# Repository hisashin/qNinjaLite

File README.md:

# Open Source $50 qLAMP machine qNinja

# $300 Real Time PCR and LAMP machine "[qNinja](https://github.com/hisashin/qNinja)" is also available

## Reference Links
- [qNinja portal](https://qninja.hisa.dev)

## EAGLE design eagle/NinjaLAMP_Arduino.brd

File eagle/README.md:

*Schematic*

*Layout for PCB*

*Layout for hand wiring*

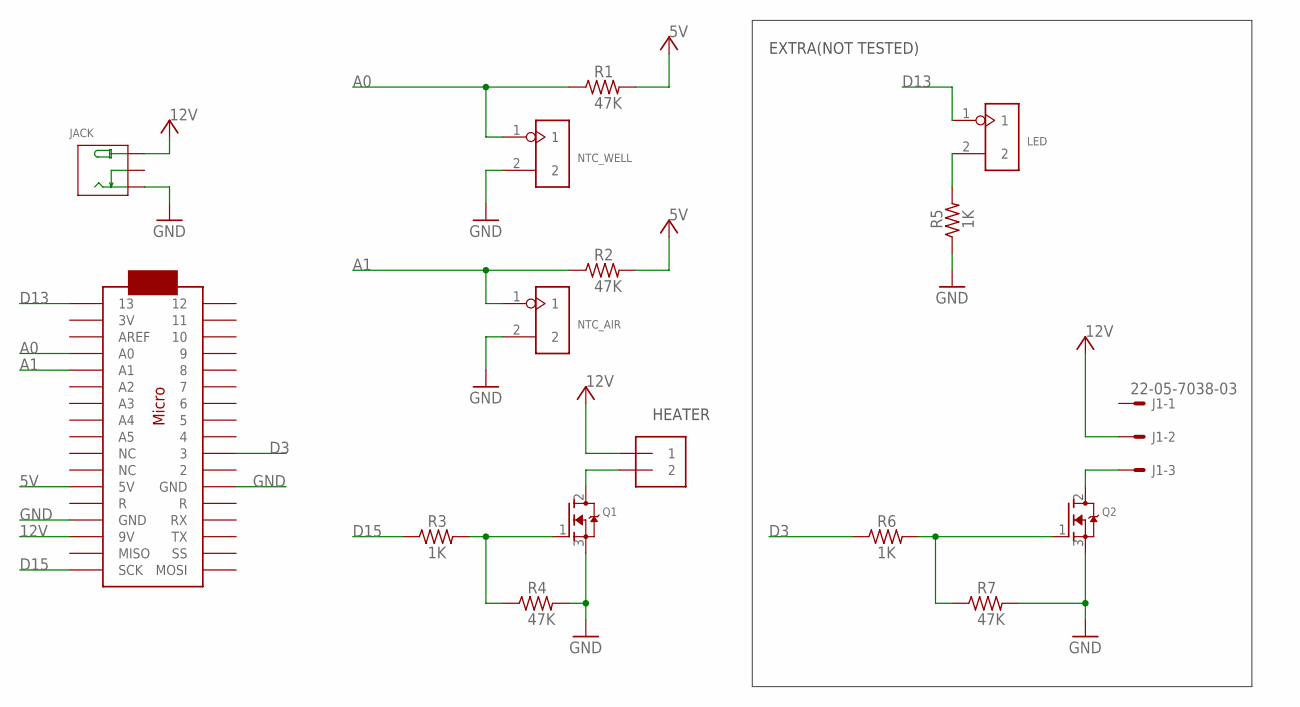
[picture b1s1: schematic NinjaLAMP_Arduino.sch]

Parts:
HEATER: 1X2-3.5MM
J1: 22-05-7038-03; 7395-03
JACK: DC-005; DCJ3P-14.2X11.0X9.0MM
LED: 2p-2.54; H2-2.54
NTC_AIR: 2p-2.54; H2-2.54
NTC_WELL: 2p-2.54; H2-2.54
Q1, Q2: MOSFET-NGDS_TO220V; TO220V
R1, R2, R4, R7: 47K; 0204/7
R3, R5, R6: 1K; 0204/7
U$2: ARDUINOMICRO

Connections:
5V: R1.2, R2.2, U$2.P$23 (5V)
12V: HEATER.1, J1.2, JACK.+B (+), JACK.+T (+), U$2.P$20 (9V)
A0: NTC_WELL.1, R1.1, U$2.P$31 (A0)
A1: NTC_AIR.1, R2.1, U$2.P$30 (A1)
D3: R6.1, U$2.P$10 (3)
D13: LED.1, U$2.P$34 (13)
D15: R3.1, U$2.P$18 (SCK)
DRAIN: HEATER.2, Q1.2 (D)
GATE: Q1.1 (G), R3.2, R4.1
GND: JACK.-1B (-), JACK.-1T (-), NTC_AIR.2, NTC_WELL.2, Q1.3 (S), Q2.3 (S), R4.2, R5.1, R7.2, U$2.P$12 (GND), U$2.P$21 (GND)
unnamed: LED.2, R5.2
unnamed: Q2.1 (G), R6.2, R7.1
unnamed: J1.3, Q2.2 (D)

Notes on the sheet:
EXTRA(NOT TESTED)
HEATER

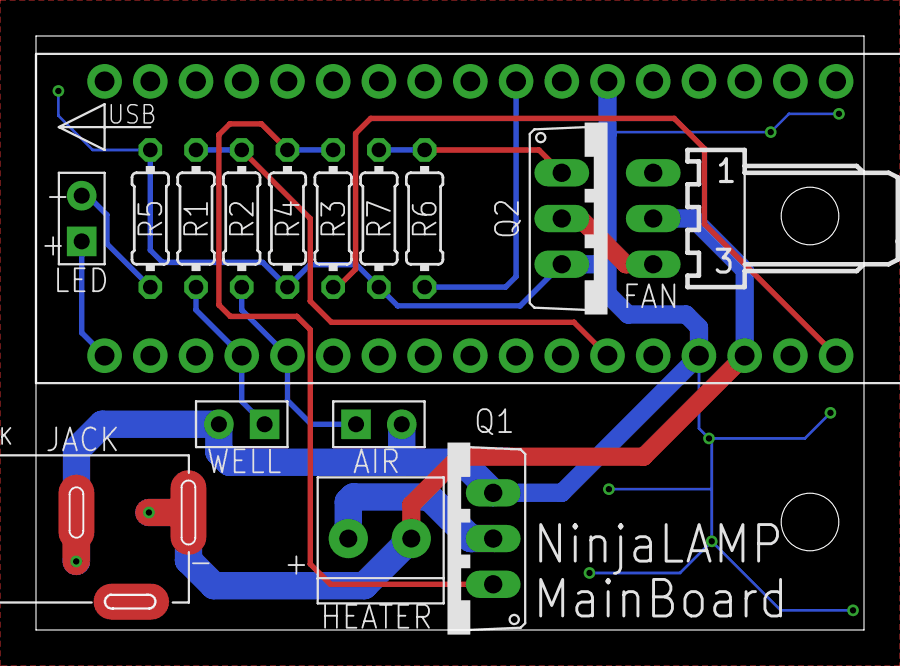
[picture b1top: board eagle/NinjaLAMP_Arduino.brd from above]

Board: 2 copper layers, 46.0 x 33.0 mm, 16 parts (0 on the bottom side), 13 nets.

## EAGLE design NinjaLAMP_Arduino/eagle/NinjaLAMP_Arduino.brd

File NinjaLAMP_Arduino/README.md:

# NinjaLAMP for Arduino

Make your own LAMP machine with Arduino.

- Why NinjaLAMP?
  - Precise temperature control with thermal simulation model sensing not only tube holder but air
  - Support different kinds of core parts guiding how to choose and calibrate to minimize error. Look "Advanced" below.
  - Easy to build. Only 4 resistors, 1 mosfet, 2 thermistors on [circuit](https://github.com/hisashin/NinjaLAMP/tree/master/NinjaLAMP_Arduino/eagle).
- [BOM (Bill of materials)](https://github.com/hisashin/NinjaLAMP/wiki/%5BArduino%5D-BOM) to buy
- 3d print [base](https://github.com/hisashin/NinjaLAMP/blob/master/NinjaLAMP_Arduino/3d/4x4_3d_base.stl) and [cover](https://github.com/hisashin/NinjaLAMP/blob/master/NinjaLAMP_Arduino/3d/4x4_3d_cover.stl) upside down without support ([3d model](https://gallery.autodesk.com/projects/149287/ninjalamp))
- Set target temperature
- [Upload source to Arduino](https://github.com/hisashin/NinjaLAMP/wiki/%5BArduino%5D-How-to-upload-the-software)
- Run and monitor temperature graph

### Advanced

- How to choose and calibrate different tube holder, heater, thermistor
- [How to use simulated sample temperature](https://github.com/hisashin/NinjaLAMP/wiki/How-to-use-simulated-sample-temperature)
- [How to customize source before uploading](https://github.com/hisashin/NinjaLAMP/wiki/%5BArduino%5D-How-to-customize-source-before-uploading)

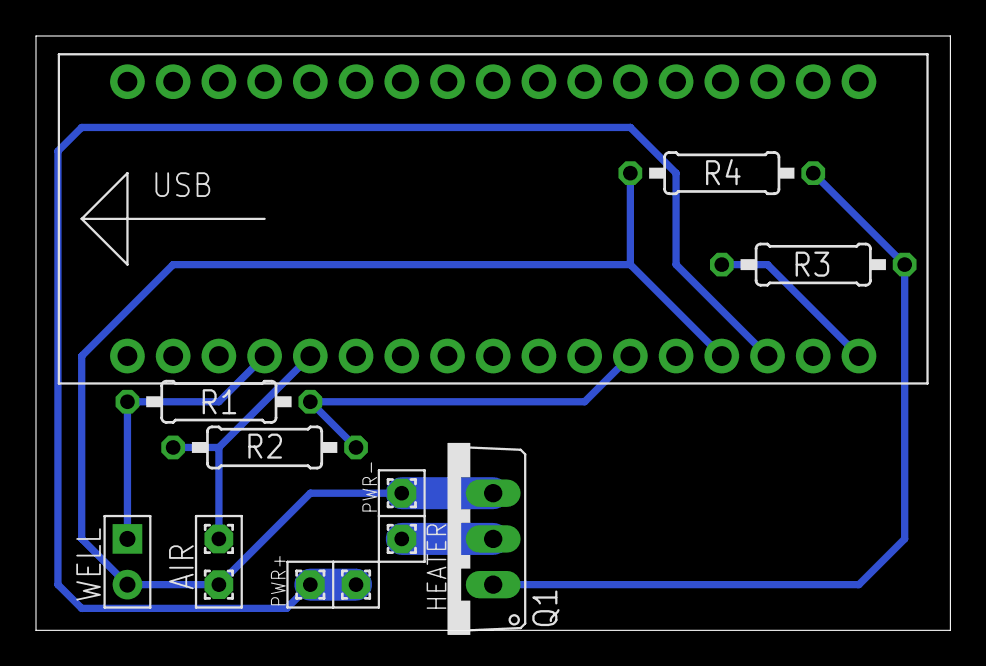
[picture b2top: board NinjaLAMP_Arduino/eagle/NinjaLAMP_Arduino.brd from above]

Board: 2 copper layers, 50.8 x 33.0 mm, 13 parts (0 on the bottom side), 8 nets.

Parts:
HEATER1, HEATER2: 1,6/0,8
NTC_AIR1, NTC_AIR2: 1,6/0,8
NTC_WELL: 2p-2.54; H2-2.54
POWER+: 1,6/0,8
POWER-: 1,6/0,8
Q1: TO220V
R1, R2, R4: 47K; 0207/10
R3: 1K; 0207/10
U$1: ARDUINOMICRO

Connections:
5V: R1.2, R2.2, U$1.P$23
12V: HEATER1.1, POWER+.1, U$1.P$20
A0: NTC_WELL.1, R1.1, U$1.P$31
A1: NTC_AIR1.1, R2.1, U$1.P$30
D15: R3.1, U$1.P$18
DRAIN: HEATER2.1, Q1.2
GATE: Q1.1, R3.2, R4.1
GND: NTC_AIR2.1, NTC_WELL.2, POWER-.1, Q1.3, R4.2, U$1.P$12

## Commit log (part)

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2020-04-27 update 3d model of Lite
2020-04-27 Implement start/stop commands
2020-04-27 Receive target temperature at "/start"
2020-04-27 Add index.html
2020-04-27 add stl data for Lite
2020-04-28 Separate ADC related functions as ADC and subclasses
2020-04-28 add eagle files
2020-04-28 add photos
2020-04-28 add 3d models
2020-04-28 Separage NinjaLAMPCore class
2020-04-28 Fix lib links / Call lib in NinjaLAMP_Arduino
2020-04-28 Fix thermistor conf (thermistors are placed to the "low" side)
2020-04-28 Move definition of PWM pin to the top
2020-04-28 Add README
2020-04-28 Add customization guide
2020-04-28 Add comments to main source file / Fix README
2020-04-28 add 3d stl
2020-04-28 add images
2020-04-29 Use symlinks to include ADC.h and NinjaLAMPCore.h/cpp
2020-04-29 Fill temp buffer before starting experiment
2020-04-29 Test
2020-04-29 Fixed a dead link
2020-04-29 Add a link to upload guide on Wiki
2020-04-29 Add image of "upload" button on Arduino IDE
2020-04-29 Add screenshot of Arduino serial monitor
2020-04-29 update 3d model : add cover
2020-04-30 add cover
2020-04-30 Add images (for customization guide)
2020-04-30 Replace images
2020-04-30 Add comments about bConstantRanges
2020-04-30 Add example connection image
2020-04-30 add belt
2020-04-30 replace photo to latest
2020-05-01 Implement temp simulation
2020-05-01 Fix merge failure
2020-05-01 Added an image for Wiki
2020-05-01 Added images for Wiki
2020-05-01 Add capture images for Wiki
2020-05-01 Move images to the right directory
2020-05-01 Add image
2020-05-01 Add illustration of heat simulation feature
2020-05-01 Add small images
2020-05-01 Add link to Wiki page
2020-05-01 New feature: Change target by serial message
2020-05-01 Add main graph (with serial target control)
2020-05-01 Add images (to illustrate how to use Arduino IDE's serial UI)
2020-05-01 Add a link to README page
2020-05-02 Arduino version become de fact NinjaLAMP
2020-05-02 Add images of Arduino's library manager
2020-05-02 Add public getters / Add elapsed time
2020-05-02 Support multiple stages
2020-05-03 Rename files (spec memo)
2020-05-03 Simplify spec memo
2020-05-03 Add URL of customization guide
2020-05-03 Add an image of thermal profile
2020-05-03 Add a link to "Experiments with multiple stages" article
2020-05-03 Add comments to getter functions
2020-05-03 Add a link to REAEMD.md (to Wiki article about output customization)
2020-05-04 t5.5 lasercut design finished
2020-05-04 eagle design finished
2020-05-04 add header
2020-05-04 remove old READMEs
2020-05-05 add simple lasercut model with t6.0mm
2020-05-16 add simple pcb
2020-05-20 add 3d model of tube_holder
2020-10-27 sync
2020-10-27 add ver1.0
2020-10-28 pcb ver1.0 complete
2020-10-29 added tacts and EEPROM
2020-10-30 added 1x8 and 2x8 iges
2020-11-06 add 3dprint data
2020-11-10 bigger footprint for polcap
2020-11-10 add todo memo
2020-11-11 Fix compilation error
2020-11-11 correct MOSFET pins
2020-11-13 add pdf and images of ver1.0 kicad
2020-11-13 Add hardware conf
2020-11-13 Define NXFT15WF104FA2B100 thermistor
2020-11-13 Implement hardware constructor (For first and second models)
2020-11-13 Define NTCG164KF104FT1S thermistor
2020-11-13 Define pins for XIAO model / Add document for LCD model
2020-11-13 add xiao example
2020-11-13 rename to README
2020-11-13 copy latest source to ver0.9 and ver1.0. They are identical at this point
2020-11-13 add image to explain version difference
2020-11-13 add image of ssd1306 library
2020-11-13 add image of xiao_example_gpio
2020-11-13 add image of xiao_example_eeprom
2020-11-13 make directory for ver0.9 and ver1.0
2020-11-13 make example directory
2020-11-13 rename to examples
2020-11-23 added example xiao_example_menu
2020-11-25 increased font size in xiao_example_menu
2020-11-25 restored sample items
2020-11-25 fixed manu name
2020-12-02 add photos and realistic menu
2020-12-12 Added lcdgfx library components to examples
2021-01-07 added utility to reset last eeprom byte, added gui_demo with initial implementation of top menu and default system configuration in eeprom
2021-01-14 initial implementation of menu
2021-01-24 Implemented edit cycle, add cycle, flip orientation and cycle run page
2021-01-25 Add a function resetting EEPROM / Clear GUI when going back to the top menu
2021-01-25 Comment-out RESET_EEPROM flag
2021-01-25 Remove unused dependency from NinjaLAMPCore lib
2021-01-26 Integrate gui_demo with NinjaLAMP core
2021-01-26 Implemented experiment management with LCD+buttons interface
2021-01-26 Add compressed core library and add how-to guide to the readme file
2021-01-26 Display temp, time and phase on the LCD
2021-01-26 Switch "Ramp", "Amplify" and "Stop" labels
2021-01-26 Call core->stop by choosing "Cancel" button on running screen
2022-03-03 just before import netlist to qLAMP-main-2x8
2022-03-03 renmaed
2022-03-03 renamed
2022-03-05 wiring
2022-03-07 dru cleared
2022-03-07 just before placing vias
2022-03-07 batch01 ready
2022-03-09 changing pd and demodulator
2022-03-10 prepare batch02/main with todo comments
2022-04-15 add equip pdf
2022-04-15 add links
2022-06-09 ordered batch2/main
2022-06-12 put latest well
2022-06-13 move dirs as qNinja
2022-06-13 move dirs unused anymore
2022-06-14 Add uPython code
2022-06-16 initialize batch03/main
2022-06-20 Add scheduler
2022-06-20 Add websocket to cycler
2022-06-26 add batch03 and batch02/pdf
2022-06-27 clear layout
2022-07-08 Add mqtt
2022-07-11 Support longer messages by MQTT
2022-08-12 just before ripup batch03/main
2022-08-12 wiring batch03/main
2022-08-14 wiring batch03/main done
2022-08-14 batch03 finished
2022-08-15 add pads below all pds
2022-08-17 add reg alt
2022-10-06 Add python files
2022-10-06 Add optics demo
2022-10-06 wiring batch04/main
2022-10-06 Add hardware control for batch3 design
2022-10-11 Implemented thermistor switching
2022-10-12 Workaround for PWM problems
2022-10-13 ordered batch04
2022-10-18 init batch05
2022-10-18 PID tuning
2022-10-26 Update PID logic
2022-10-26 Enable & disable buttons according to the device state
2022-10-27 update dxf
2022-11-01 PID control / UI
2022-11-01 Add cycler_mqtt
2022-11-03 Add LCD
2022-11-03 autodeploy
2022-11-03 Remove unused file
2022-11-04 Support batch4 pins
2022-11-04 Add console
2022-11-06 Move app files into app dir
2022-11-07 wired batch05/main
2022-11-08 thick holder to remove washers
2022-11-22 Support batch5 hardware
2022-11-22 Update web client
2022-11-22 Fix merge error
2022-11-23 Change app name
2022-11-23 Collapse advanced settings
2022-11-23 Update status bar layout
2022-11-23 Update form
2022-11-24 Add experiment protocol to event payload
2022-11-24 Add toasts
2022-11-24 Add advanced menu
2022-11-24 Change topic level (qninjalite->ninja)
2022-11-24 Add toasts to show connection status
2022-11-24 Shorten MQTT property names
2022-11-24 Shorten MQTT properties / Change file naming rule
2022-11-25 Shorten property names (final_hold_temp->h)
2022-11-25 Shorten property names (data_collection_interval->i)
2022-11-25 Shorten MQTT property names (data_collection -> c)
2022-11-25 Shorten property names (duration->d)
2022-11-25 Replace property names (temp->t)
2022-11-25 Replace property name (steps->s)
2022-11-25 Update default protocol
2022-11-25 Replace property names (PID conf)
2022-11-25 Change MQTT property names (PID)
2022-11-25 Build
2022-11-25 Fetch protocols with MQTT
2022-11-26 Fetch protocols after connecting to the server
2022-11-26 Update console
2022-11-28 Use topic filter "aws/#"
2022-11-29 Fetch experiment list by MQTT API
2022-11-29 Implement experiment loading
2022-12-01 Implemented protocol management feature
2022-12-01 Remove debug button
2022-12-01 Request new experiment ID to AWS
2022-12-01 Fixed scrolling bug of temperature chart
2022-12-02 Fix scrolling bug
2022-12-02 Update dist dir
2022-12-02 Add download link / permanent link
2022-12-02 Add timestamp file
2022-12-02 Update test
2022-12-02 update timestamp
2022-12-02 quote paths
2022-12-04 Workaround for the updated device status logic
2022-12-05 Use device presence API
    * Replace ping logic with presence API
    * Add JSON/CSV button to progress monitor
2022-12-06 Update status request seqence
2022-12-06 Add favicon
2022-12-06 Update favicon
2022-12-06 tmp test
2022-12-06 remove
2022-12-07 Change graph range settings
2022-12-09 Add tid and remove uid
2022-12-12 Support integer labels when processing "progress" objects
2022-12-13 Fix label message
2022-12-13 Skip progress updates / Define integer labels to represent step states
2022-12-13 Update MQTT logic
    * Publish to state topic on boot
    * Publish to "state" topic on transition
2022-12-13 Stop sending to dt/# topics after experiment
2022-12-13 Remove debug labels
2022-12-14 Show Finish button after experiment
2022-12-14 Remove ping & ping-res from cycler_mqtt
2022-12-14 Joining an ongoing experiment
2022-12-26 Set protocol when showing ProtocolEditor
2023-01-17 ordered b6
2023-02-10 add batch7
2023-02-24 wiring batch7
2023-02-28 wiring batch7 main
2023-03-12 modeling ver0.4 complete
2023-03-13 add 3d model of stl-ver0.4
2023-04-27 soldered batch07/main
